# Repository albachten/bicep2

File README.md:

# Bicep2 - Flexing my "ARM" muscles

This is a simple ARM Cortex M0 development board with:
* SAMD21G18A cpu
* 0.96" OLED I2C display
* LiPo battery
* 2 I2C connectors (1 QWIIC and 1 header)
* 1 extra serial connector
* 1 rotary switch
* 4 pushbuttons
* 4 LEDs
* 1 neopixel LED
* 2 MB SPI flash

This is designed for prototyping.
I find that almost every time I'm trying new hardware I need some combination of LEDs, buttons, rotary switch, or an OLED display.
The display is connected to the I2C bus and can be disconnected by removing the jumper resistors.
The switches and LEDs can be connected to digital pins with jumper wires.

The SPI flash enables using the same bootloader as the adafruit feather m0 express.  This memory is typically used for CircuitPython but can also be used for general storage.

[Schematic pdf](v1.0/bicep2.pdf)

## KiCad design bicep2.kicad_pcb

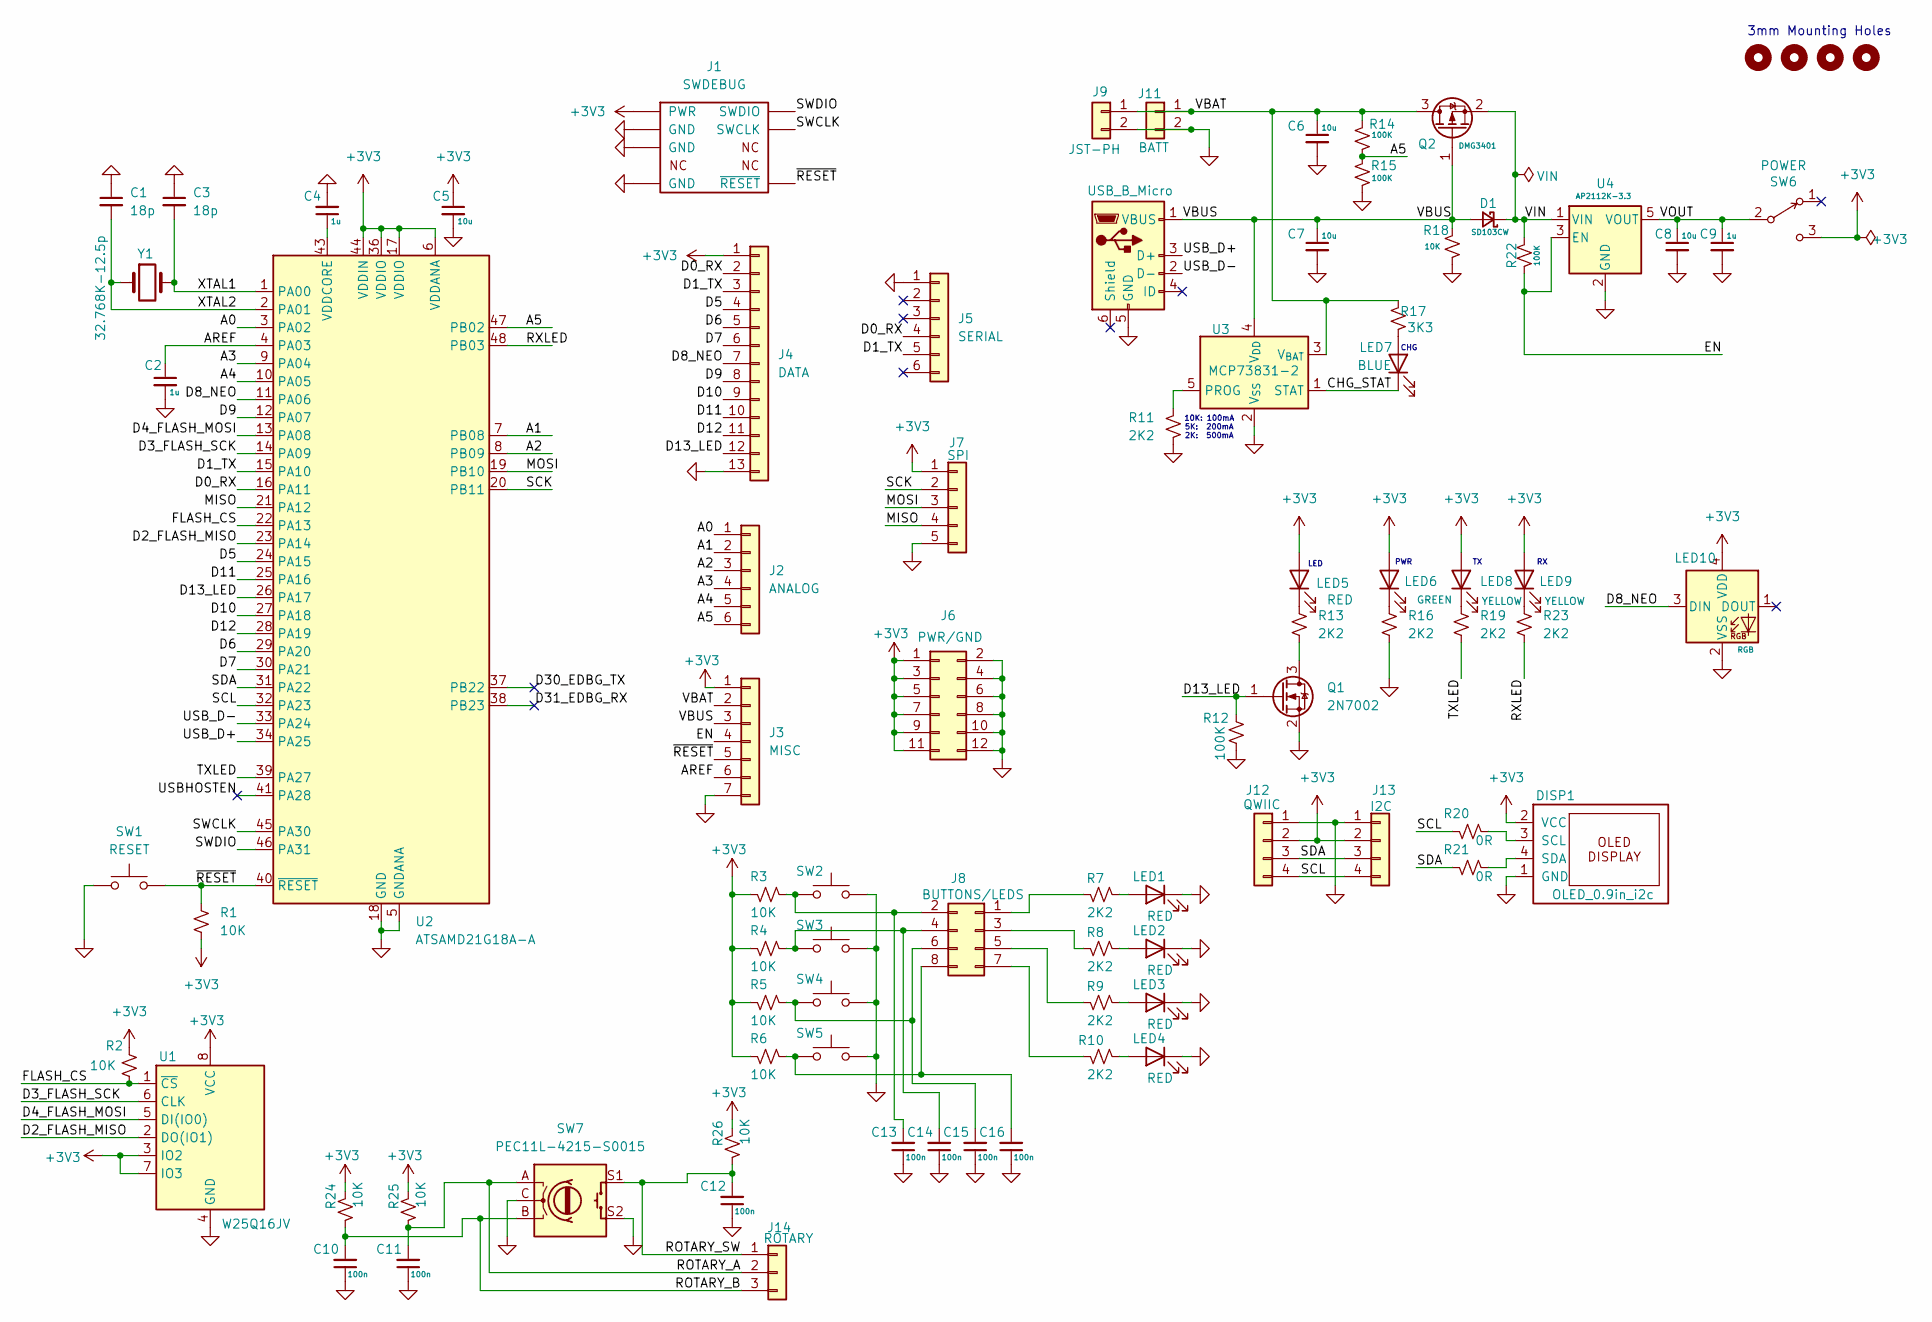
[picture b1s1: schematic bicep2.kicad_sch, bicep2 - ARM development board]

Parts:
C1, C3: 18p; C_0805_2012Metric
C2, C4, C9: 1u; C_0805_2012Metric
C5, C6, C7, C8: 10u; C_0805_2012Metric
C10, C11, C12, C13, C14, C15, C16: 100n; C_0805_2012Metric
D1: SD103CW; D_SOD-123
DISP1: OLED_0.9in_i2c; OLED_0.9in_i2c_weewooday
H1, H2, H3, H4: MountingHole_Pad; MountingHole_3.2mm_M3_ISO7380_Pad
J1: SWDEBUG; CortexDebug
J2: ANALOG; PinHeader_1x06_P2.54mm_Vertical
J3: MISC; PinHeader_1x07_P2.54mm_Vertical
J4: DATA; PinHeader_1x13_P2.54mm_Vertical
J5: SERIAL; PinHeader_1x06_P2.54mm_Vertical
J6: PWR/GND; PinHeader_2x06_P2.54mm_Vertical
J7: SPI; PinHeader_1x05_P2.54mm_Vertical
J8: BUTTONS/LEDS; PinHeader_2x04_P2.54mm_Vertical
J9: JST-PH; JST_PH_S2B-PH-SM4-TB_1x02-1MP_P2.00mm_Horizontal
J10: USB_B_Micro; USB_Micro-B_Amphenol_10118194_Horizontal
J11: BATT; PinHeader_1x02_P2.54mm_Vertical
J12: QWIIC; QWIIC_JST_SH_BM04B-SRSS-TB_1x04-1MP_P1.00mm_Vertical
J13: I2C; PinHeader_1x04_P2.54mm_Vertical
J14: ROTARY; PinHeader_1x03_P2.54mm_Vertical
LED1, LED2, LED3, LED4, LED5: RED; LED_0805_2012Metric
LED6: GREEN; LED_0805_2012Metric
LED7: BLUE; LED_0805_2012Metric
LED8, LED9: YELLOW; LED_0805_2012Metric
LED10: RGB; LED_WS2812B-2020_PLCC4_2.0x2.0mm
Q1: 2N7002; SOT-23
Q2: DMG3401; SOT-23
R1, R2, R3, R4, R5, R6, R18, R24, R25, R26: 10K; R_0805_2012Metric
R7, R8, R9, R10, R11, R13, R16, R19, R23: 2K2; R_0805_2012Metric
R12, R14, R15, R22: 100K; R_0805_2012Metric
R17: 3K3; R_0805_2012Metric
R20, R21: 0R; R_0805_2012Metric
SW1: RESET; TL3305B_SPST_PushButton
SW2, SW3, SW4, SW5: TL3305B; TL3305B_SPST_PushButton
SW6: POWER; EG1218_SPDT_Slide_Switch
SW7: PEC11L-4215-S0015; RotaryEncoder_Alps_EC11E-Switch_Vertical_H20mm
U1: W25Q16JV; SOIC-8_5.23x5.23mm_P1.27mm
U2: ATSAMD21G18A-A; TQFP-48_7x7mm_P0.5mm
U3: MCP73831-2; SOT-23-5
U4: AP2112K-3.3; SOT-23-5
Y1: 32.768K-12.5p; Crystal_SMD_G8-2Pin_3.2x1.5mm

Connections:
+3V3: C5.1, DISP1.2 (VCC), J1.1 (PWR), J3.1, J4.1, J6.1, J6.3, J6.5, J6.7, J6.9, J6.11, J7.1, J12.2, J13.2, LED5.2 (A), LED6.2 (A), LED8.2 (A), LED9.2 (A), LED10.4 (VDD), R1.2, R2.2, R3.1, R4.1, R5.1, R6.1, R24.2, R25.2, R26.2, SW6.3 (C), U1.3 (IO2), U1.7 (IO3), U1.8 (VCC), U2.6 (VDDANA), U2.17 (VDDIO), U2.36 (VDDIO), U2.44 (VDDIN)
/A0: J2.1, U2.3 (PA02)
/A1: J2.2, U2.7 (PB08)
/A2: J2.3, U2.8 (PB09)
/A3: J2.4, U2.9 (PA04)
/A4: J2.5, U2.10 (PA05)
/A5: J2.6, R14.1, R15.2, U2.47 (PB02)
/AREF: C2.1, J3.6, U2.4 (PA03)
/CHG_STAT: LED7.1 (K), U3.1 (STAT)
/D0_RX: J4.2, J5.4, U2.16 (PA11)
/D1_TX: J4.3, J5.5, U2.15 (PA10)
/D2_FLASH_MISO: U1.2 (DO(IO1)), U2.23 (PA14)
/D3_FLASH_SCK: U1.6 (CLK), U2.14 (PA09)
/D4_FLASH_MOSI: U1.5 (DI(IO0)), U2.13 (PA08)
/D5: J4.4, U2.24 (PA15)
/D6: J4.5, U2.29 (PA20)
/D7: J4.6, U2.30 (PA21)
/D8_NEO: J4.7, LED10.3 (DIN), U2.11 (PA06)
/D9: J4.8, U2.12 (PA07)
/D10: J4.9, U2.27 (PA18)
/D11: J4.10, U2.25 (PA16)
/D12: J4.11, U2.28 (PA19)
/D13_LED: J4.12, Q1.1 (G), R12.1, U2.26 (PA17)
/D30_EDBG_TX: U2.37 (PB22)
/D31_EDBG_RX: U2.38 (PB23)
/EN: J3.4, R22.1, U4.3 (EN)
/FLASH_CS: R2.1, U1.1 (~CS), U2.22 (PA13)
/MISO: J7.4, U2.21 (PA12)
/MOSI: J7.3, U2.19 (PB10)
/ROTARY_A: C11.2, J14.2, R25.1, SW7.A
/ROTARY_B: C10.2, J14.3, R24.1, SW7.B
/ROTARY_SW: C12.2, J14.1, R26.1, SW7.S1
/RXLED: R23.2, U2.48 (PB03)
/SCK: J7.2, U2.20 (PB11)
/SCL: J12.4, J13.4, R20.1, U2.32 (PA23)
/SDA: J12.3, J13.3, R21.1, U2.31 (PA22)
/SWCLK: J1.4 (SWCLK), U2.45 (PA30)
/SWDIO: J1.2 (SWDIO), U2.46 (PA31)
/TXLED: R19.2, U2.39 (PA27)
/USBHOSTEN: U2.41 (PA28)
/USB_D+: J10.3 (D+), U2.34 (PA25)
/USB_D-: J10.2 (D-), U2.33 (PA24)
/VBAT: C6.1, J3.2, J9.1, J11.1, Q2.3 (D), R14.2, R17.1, U3.3 (V_{BAT})
/VBUS: C7.1, D1.2 (A), J3.3, J10.1 (VBUS), Q2.1 (G), R18.2, U3.4 (V_{DD})
/VIN: D1.1 (K), Q2.2 (S), R22.2, U4.1 (VIN)
/VOUT: C8.1, C9.1, SW6.2 (B), U4.5 (VOUT)
/XTAL1: C3.2, U2.1 (PA00), Y1.2
/XTAL2: C1.2, U2.2 (PA01), Y1.1
/~RESET: J1.10 (~RESET), J3.5, R1.1, SW1.2, U2.40 (~RESET)
GND: C1.1, C2.2, C3.1, C4.2, C5.2, C6.2, C7.2, C8.2, C9.2, C10.1, C11.1, C12.1, C13.1, C14.1, C15.1, C16.1, DISP1.1 (GND), J1.3 (GND), J1.5 (GND), J1.9 (GND), J3.7, J4.13, J5.1, J6.2, J6.4, J6.6, J6.8, J6.10, J6.12, J7.5, J9.2, J10.5 (GND), J11.2, J12.1, J13.1, LED1.1 (K), LED2.1 (K), LED3.1 (K), LED4.1 (K), LED10.2 (VSS), Q1.2 (S), R11.2, R12.2, R15.1, R16.2, R18.1, SW1.1, SW2.1, SW3.1, SW4.1, SW5.1, SW7.C, SW7.S2, U1.4 (GND), U2.5 (GNDANA), U2.18 (GND), U2.35 (GND), U2.42 (GND), U3.2 (V_{SS}), U4.2 (GND)
unnamed: DISP1.3 (SCL), R20.2
unnamed: DISP1.4 (SDA), R21.2
unnamed: J8.1, R7.1
unnamed: C13.2, J8.2, R3.2, SW2.2
unnamed: J8.3, R8.1
unnamed: C14.2, J8.4, R4.2, SW3.2
unnamed: J8.5, R9.1
unnamed: C15.2, J8.6, R5.2, SW4.2
unnamed: J8.7, R10.1
unnamed: C16.2, J8.8, R6.2, SW5.2
unnamed: LED1.2 (A), R7.2
unnamed: LED2.2 (A), R8.2
unnamed: LED3.2 (A), R9.2
unnamed: LED4.2 (A), R10.2
unnamed: LED5.1 (K), R13.1
unnamed: LED6.1 (K), R16.1
unnamed: LED7.2 (A), R17.2
unnamed: LED8.1 (K), R19.1
unnamed: LED9.1 (K), R23.1
unnamed: Q1.3 (D), R13.2
unnamed: C4.1, U2.43 (VDDCORE)
unnamed: R11.1, U3.5 (PROG)

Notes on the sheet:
PWR
3mm Mounting Holes
10K: 100mA 5K: 200mA 2K: 500mA
LED
CHG

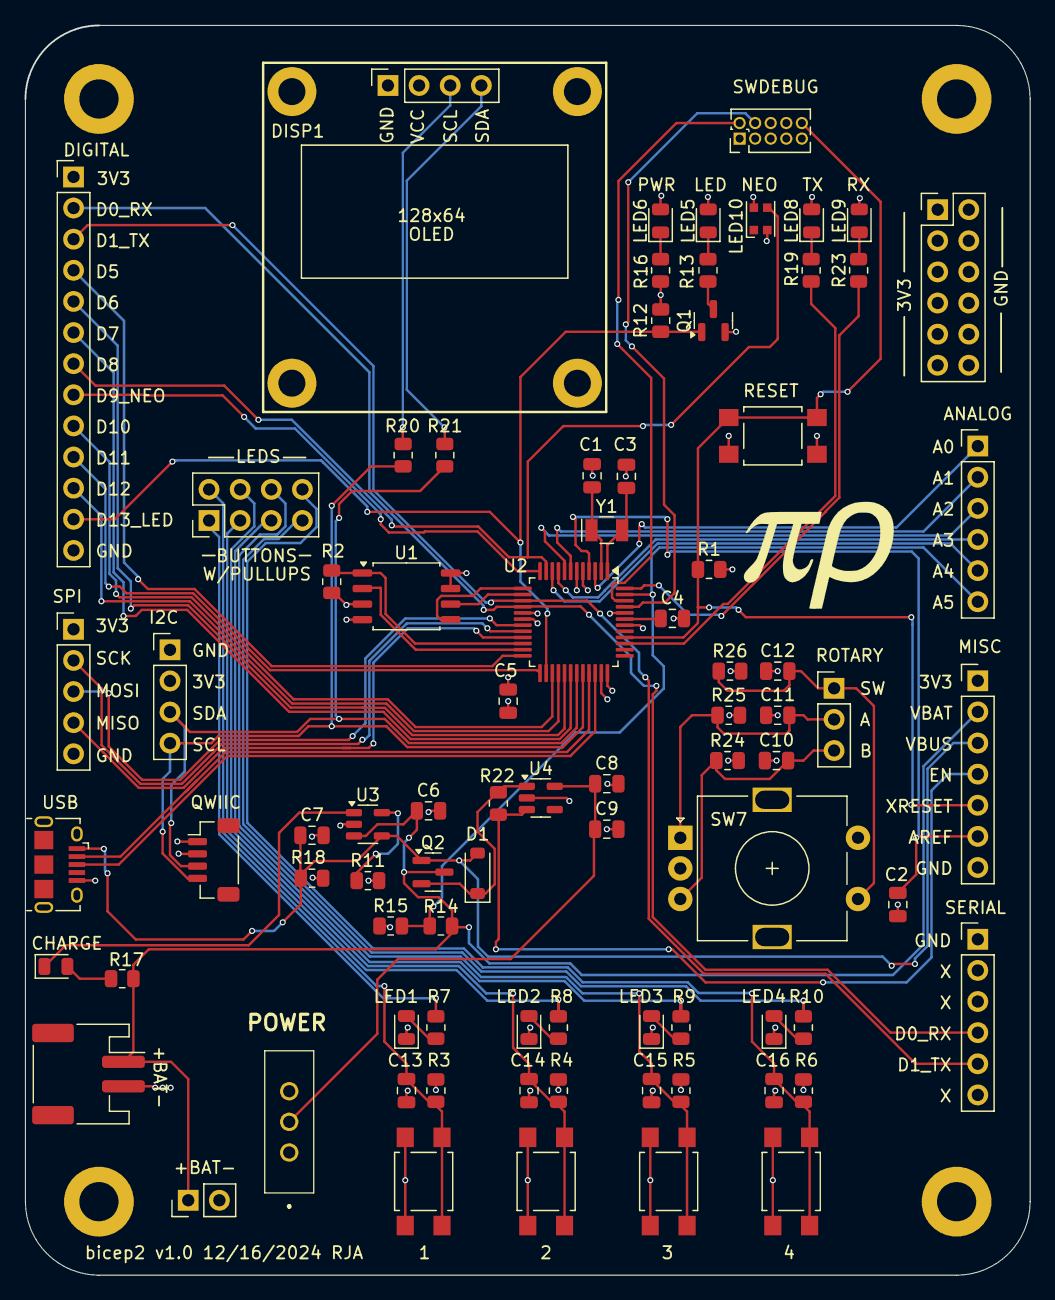
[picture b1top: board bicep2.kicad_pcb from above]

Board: 4 copper layers, 82.0 x 102.0 mm, 88 parts (1 on the bottom side), 69 nets.

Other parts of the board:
G1: LOGO; pirho_0.50
G2: LOGO; pirho

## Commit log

2024-12-16 v1.0
